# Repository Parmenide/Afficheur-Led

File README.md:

# Élèvage - Afficheur Led.

Un afficheur à diodes électroluminescentes pour faciliter l'appel et la consultation de classes dans une cour d'établissement scolaire du premier cycle du secondaire.

- [Description](#description-)
- [Péripheriques](#périphériques-)
- [Caractéristiques techniques :](caractéristiques-techniques-)
- [Composition matérielle :](#composition-matérielle-)
- [Procédure d'utilisation](#procédure-dutilisation-)
- [Sécurité](#sécurité-)
- [Notes complémentaires](notes-complementaires-)
- [Versions et mises à jours](#versions-et-mises-à-jours)
- [Explications résumée du fonctionnement](#explication-résumée-du-fonctionnement)
- [Illustrations](#illustrations)

## Description :

Cet afficheur à diodes électroluminescentes a pour fonction de fournir au service de vie scolaire d'un collège un support de communication simplifié avec les élèves, en particulier pour l'appel des classes à la cantine ou au réfectoire. Celui-ci par ailleurs, offre aux élèves un moyens aisé de se rapporter aux informations communiquées.
L'appareil affiche alors les classes souhaitées (de la 6eme à la 3eme reparties en classes identifiées de A à E) relativement à un tableau de commande qui transmet par radio-fréquences l'appel effectué.
Les classes appelées sont affichées en rouge et clignotent pendant 5 minutes avant de se stabiliser. Cela afin de distinguer les classes les plus récemment appelées des plus anciennes.

## Périphériques :

* Afficheur à diodes électroluminescentes
* Tableau de commande
* Relais

## Caractéristiques techniques :

 • | Afficheur | Tableau de commande | Relais
------------ | ------------ | ------------- | -------------
Tension de fonctionnement | 220v             | 220v            | 220v
Dimensions (≈)            | 1265mm/260mm/60mm | 225mm/160mm/50mm | ?mm/?mm/?mm
Emission/réception min.   | 100m             | 100m             | 100m
Emission/réception max    | 100m             | 100m             | 100m

## Composition matérielle :

* Afficheur
    * Cable étamé 26 AWG ≈20m
    * 777x leds 620\~625nm, 150\~200mcd, 1.8\~2.2v, 20mA.
    * 5x Panneaux MDF, A3, épaisseur : 3mm.
    * 3x SN74HC595
    * 20x P2N2222A
    * 20x Resistances 1KΩ
    * 4x Connecteur mâle (KF2510)
    * 4x Connecteur femelle (KF2510)
    * 20x Broches à sertirs (KF2510)
    * 1x PCB prototype 120mm/80mm
    * 1x Arduino-pro-mini 5V (ATMEGA 328)
    * 1x Récepteur RF 440mhz (HCN67)
    * 1x Antenne (170mm)
    * 200x Resistances 220Ω
    * 1x Transformateur AC/DC, 5V, 8A

* Tableau de commandes
    * 1x Cable étamé 26 AWG ≈1m
    * 20x led 620\~625nm, 150\~ 200mcd, 1.8\~ 2.2v, 20mA.
    * 1x Arduino-pro-mini 5V (ATMEGA 328)
    * 2x Panneaux MDF, A3, épaisseur : 3mm
    * Cable étamé 26 AWG ≈1m
    * Cable étamé 30 AWG ≈1m
    * 1x L7805
    * 2x CD4051
    * 20x Interupteur (MTS 101)
    * 2x Embases (DC3-10)
    * 2x Connecteurs (FC-10)
    * 1x PCB prototype 90mm/70mm
    * 1x Emeteur RF 440mhz (HC34C)
    * 1x Antenne (170mm)
    * 1x Transformateur AC/DC, 12V, 1A
    
* Relais
    * 2x led 620\~625nm, 150\~ 200mcd, 1.8\~ 2.2v, 20mA.
    * 1x Arduino-pro-mini 5V (ATMEGA 328)
    * 1x L7805
    * 1x PCB prototype 90mm/70mm
    * 1x Récepteur RF 440mhz (HCN67)
    * 1x Emeteur RF 440mhz (HC34C)
    * 2x Antenne (170mm)
    * 1x Transformateur AC/DC, 12V, 500mA

## Procédure d'utilisation :
L'utilisation demeure des plus simples : lorsque les deux appareils sont sous tensions, l'activation d'une classe sur le tableau de commandes allume la classe correspondante sur le panneau d'affichage. Les classes appelées clignotes pendant cinq minutes avant de rester allumées, cela afin de distinguer les classes récemment appelées des plus anciennes.

## Sécurité :
Si l'appareil est conçu pour résister aux projections d'eau et à l'humidité, il n'est pas conçu pour être immergé dans un liquide.

## Notes complémentaires :
Cet afficheur fut conçu avec les moyens techniques à disposition, à savoir une découpeuse laser pour le recouvrement qui contraint à une surface de découpe de la taille d'un A3 maximum.
Du côté électronique, là aussi le manque de moyens ont conduit à des choix spécifiques. Ainsi, à defaut de pouvoir graver un circuit sur une plaque de cuivre, il fut choisi d'utiliser des cartes de prototypage ainsi que des modules plutôt que des composants (AT-MEGA et radios-transmeteurs notamment).
L'afficheur serait alors sûrement d'autant mieux conçu s'il pouvait ne pas être soumis aux contraintes précédemment évoquées et donc permettre la découpe en une seule pièce des faces de l'afficheur, ainsi que de proposer un circuit plus abouti pour l'électronique.

Pour plusieurs autres raisons diverses, il fut choisi de composer des lettres et chiffres par plusieurs leds juxtaposés. Ce choix conduit à de lourdes opérations de fabrication. De plus, il n'est pas sans augmenter le risque de défaillance du système complet puisque, chaque led (777 au total) est potentiellement sujet à un risque de disfonctionnement. Réfléchir à un système moins complexe, mais tout aussi efficace serait alors sûrement souhaitable dans l'amélioration de cet objet.

Du coté logiciel, des améliorations sont sûrement aussi à envisager :
- Inverser les valeurs envoyé et reçu par le récepteur qui sont contraire à l'usage habituel, rendant le code parfois contre-intuitif (en effet, les 0 signifient ouverts et les 1 fermés dans la programmation actuelle)
- Ajouter un système de gestion par le biais du moniteur permettant de modifier le temps de clignotement ou la puissance des leds.
- Synchroniser le clignotement des leds pour l'afficheur

Afin de permettre d'éventuelles améliorations, les fichiers originaux de découpe ainsi que les fichiers correspondant aux circuits imprimé sont disponibles dans ce Git.

## Versions et mises à jours
L'ensemble est diffusé initialement dans sa version 1.0. C'est cette version qui accompagne l'appareil initialement fabriqué.
Dans le souci de proposer des améliorations sans contraindre l'utilisation et l'entretient de l'appareil initialement conçu, la version 1.0 restera acessible en plus des versions mises à jours.
Pour d'éventuelles mises à jour de la programmation des différents ATMEGA, il faudra se munir d'un programmateur UART (sur la base d'un microcontrôleur cp2101 par exemple).

## Explication résumée du fonctionnement.
### Tableau de bord
#### Menuiserie
- Conçu à partir de plans de découpe réalisés par ordinateur, c'est à partir d'une surface limitée à un A3 que fut découpé au laser les éléments du tableau de bord.
- Les interrupteurs, circuits de fils ainsi que les leds incrustés, furent montés sur le panneau avant son assemblage. Cela fait, les autres parties du tableau de bord furent assemblés par collage puis peints avant d'ajouter la face avant et les interrupteurs montés sur celui-ci.
#### Électronique
- 20 circuits sous tensions comprenant une led et un interrupteur constitue chaque boutons correspondant à chaque classe du tableau de bord.
- Sur chacun de ces circuits, un raccord à une broche du microcontrôleur (ATMEGA325) est effectué.
- Le microcontrôleur ne comprenant pas assez d'entrés/sorties, il fut choisi d'utiliser un multiplexeur/demultiplexeur (CD4051 ou SN74HC595) permettant par quelques broches de commander ou recevoir plusieurs signaux.
- Chaque signaux reçu par le microcontrôleur est rapporté à un bit nul ou positif (ouvert ou fermé) identifiant chaque classe à allumer ou éteindre.
- Ces signaux mémorisés dans un tableau, sont envoyés par le module de radio-frequence (À l'aide de la bibliotheque [VirtualWire](http://www.airspayce.com/mikem/arduino/VirtualWire.pdf))
### Afficheur
#### Menuiserie
- Conçu à partir de plans de découpe réalisés par ordinateur, c'est à partir d'une surface limitée à un A3 que fut découpé au laser les éléments de l'afficheur.
- Dans un premier temps, les éléments structurels de l'afficheur furent peints, puis les leds ajoutés sur les éléments de la façade de l'afficheur avant d'êtres englués pour les maintenir en place.
- Des fils dénudés furent ensuite glissés entre les différentes anodes puis cathode des leds avant de souder ces fils pour raccorder les leds entres elles (par groupe de 4 leds monté en série). Est ensuite soudé des fils aux différents groupes de leds pour permettre leurs raccordements au microcontrôleur.
- À l'aide de tasseau de 10x10mm placés aux arêtes de l'afficheur, les différents éléments de la façade sont rassemblés et collés.
- L'ensemble est vernis et raccordé à l'électronique.
#### Électronique
- 20 circuits sous tensions correspondant à chaque classe et comprenant en moyenne 30 leds répartie en séries de 4 leds rassemblés en parallèles. Chacun de ces circuits est ouvert et comporte un fil qui une fois raccordé à l'anode du générateur permet fermer le circuit et donc d'afficher la classe correspondante.
- Chacun de ces fils est raccordé au collecteur d'un transistor (P2N2222A) qui a son émetteur raccordé à l'anode du générateur. En alimentant ou non la base du transistor, on peut alors utiliser celui-ci comme interrupteur électronique.
- Chaque base de chaque transistor (20 en tout) est raccordée à une borne du microcontrôleur par le biais d'un multiplexeur/demultiplexeur.
- De ce, à la réception du signal, chaque transistor est alimenté ou non à sa base selon l'information recu (0 ou 1).

## Illustrations
### Panneau d'affichage V 1.0
     
### Tableau de commandes V 1.0
 
### Mise en situation dans un collège de région tourangelle

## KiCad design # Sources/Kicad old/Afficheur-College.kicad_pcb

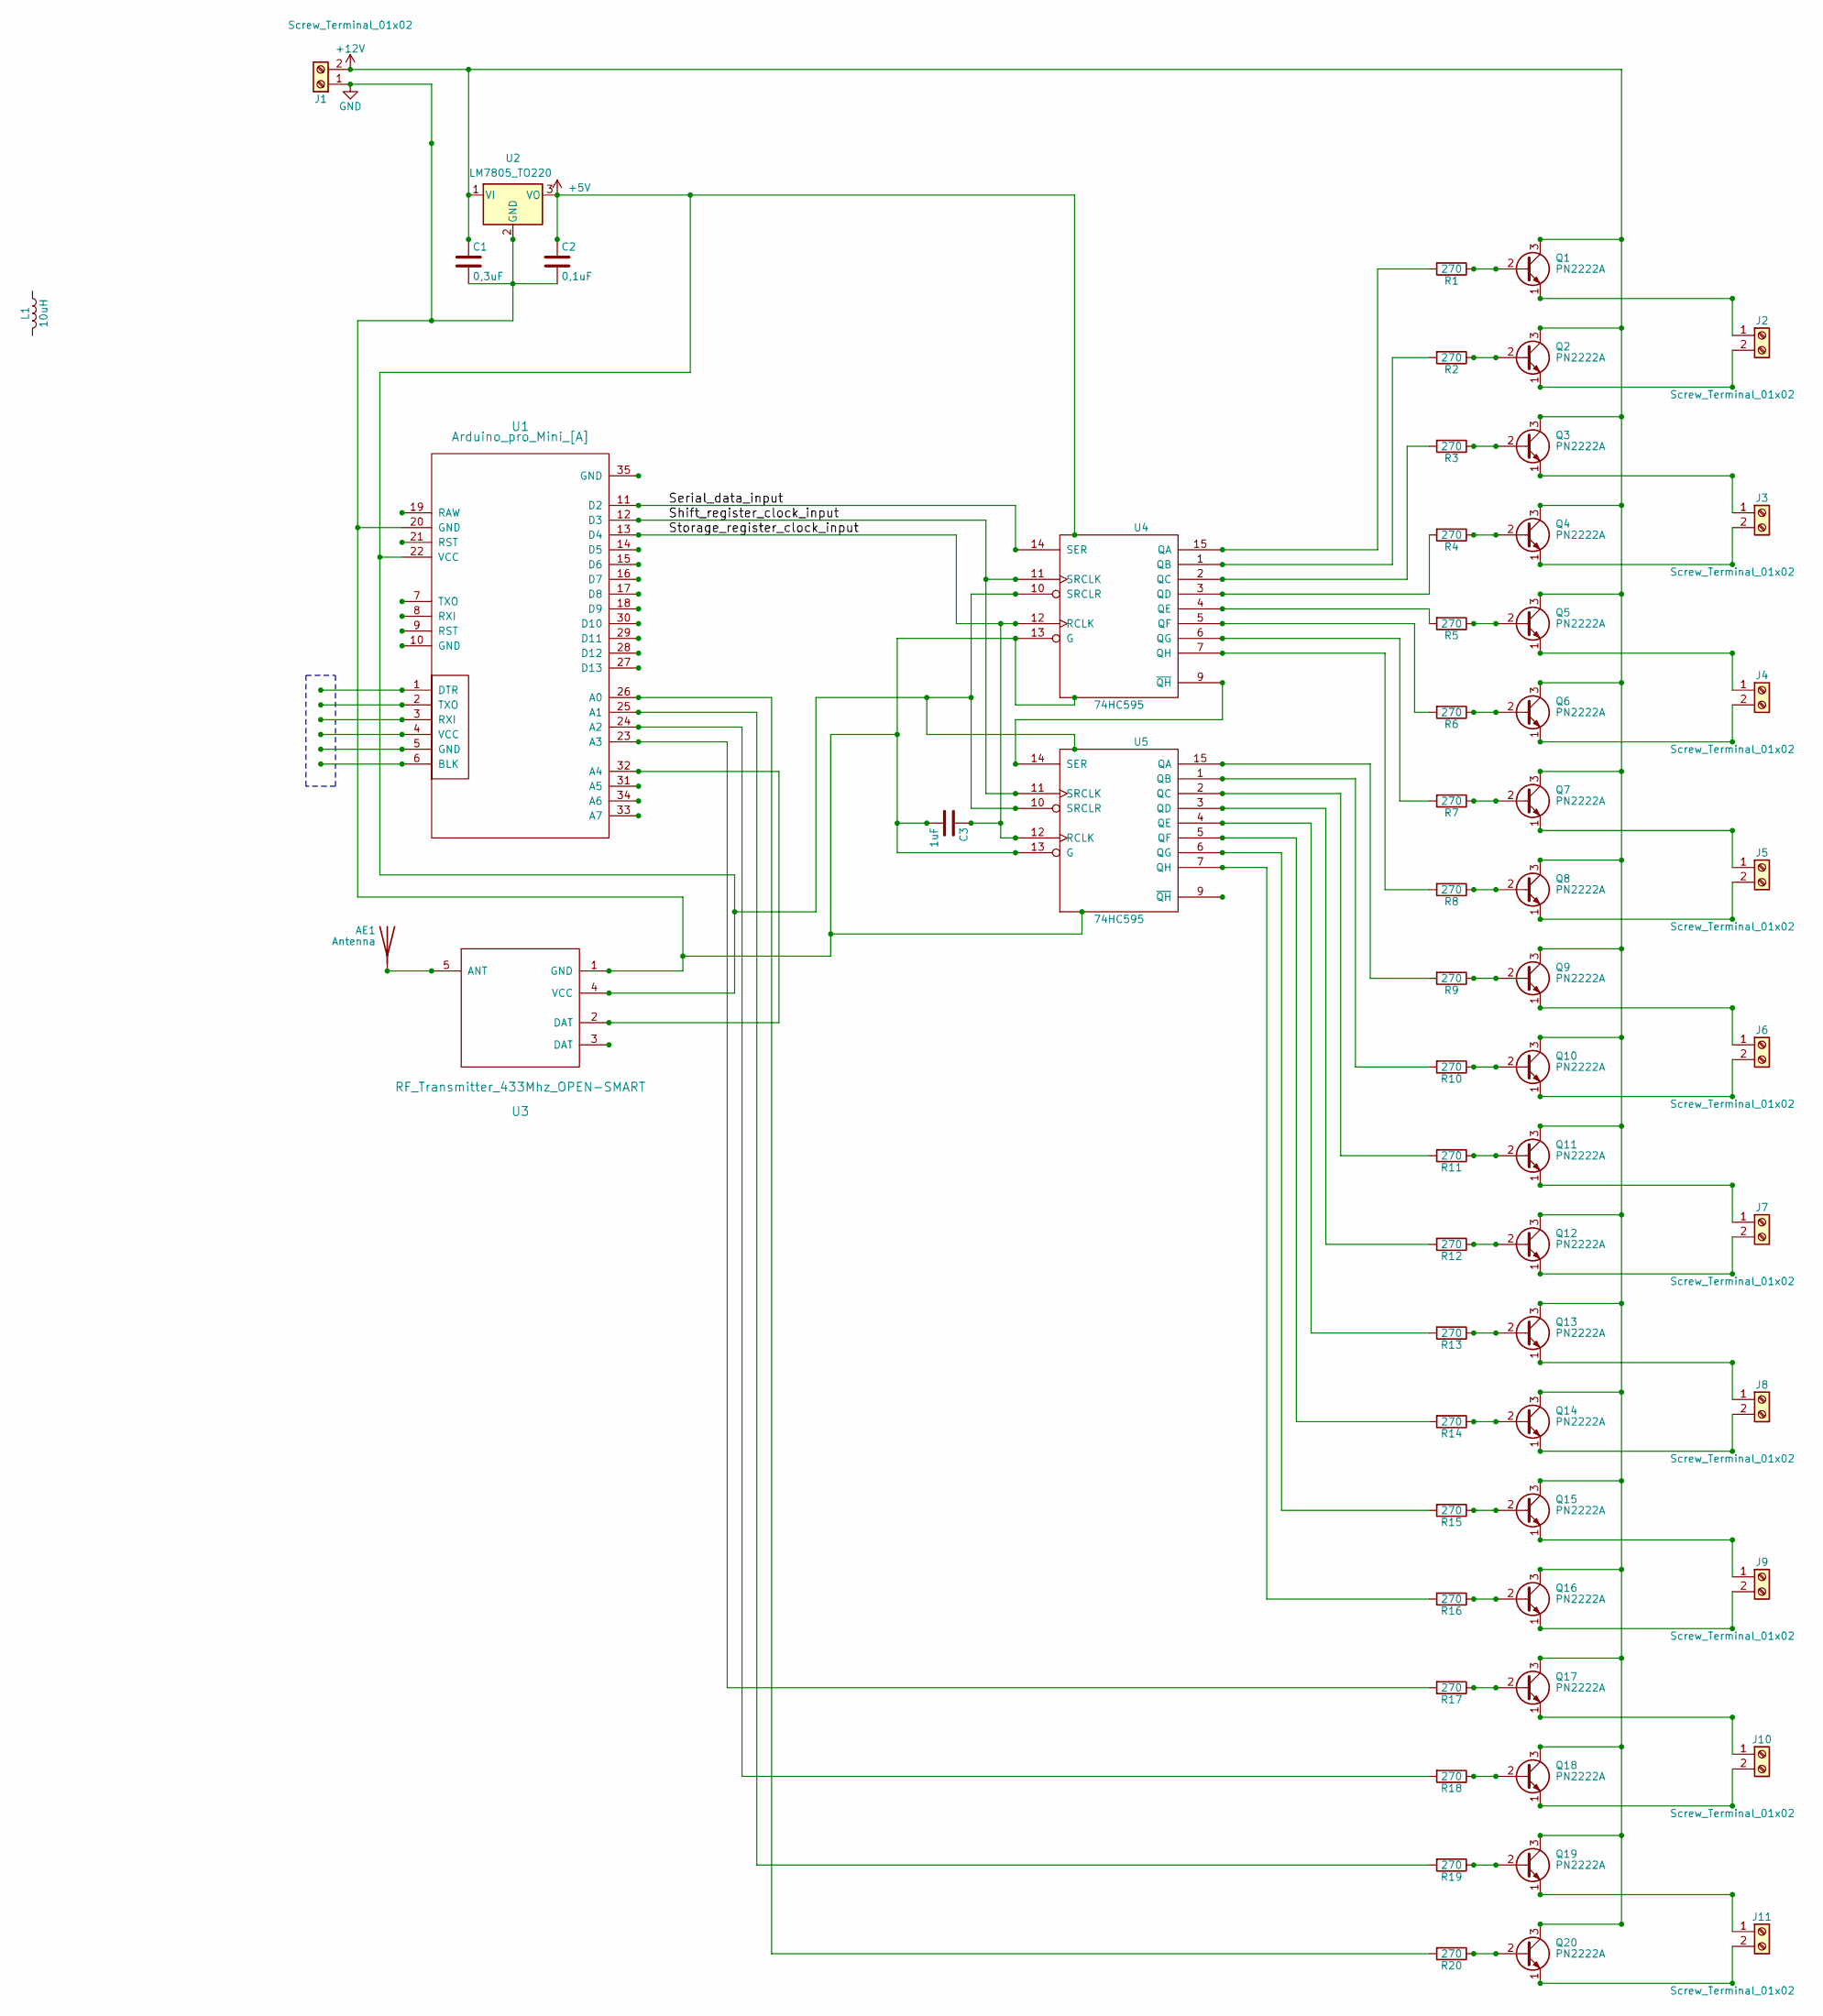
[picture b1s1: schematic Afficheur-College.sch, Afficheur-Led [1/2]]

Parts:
AE1: Antenna; 1pin
C1: 0,3uF; C_Disc_D5.0mm_W2.5mm_P5.00mm
C2: 0,1uF; C_Disc_D5.0mm_W2.5mm_P5.00mm
C3: 1uF; C_Disc_D5.0mm_W2.5mm_P5.00mm
J1, J2, J3, J4, J5, J6, J7, J8, J9, J10, J11: Screw_Terminal_01x02; TerminalBlock_Pheonix_MPT-2.54mm_2pol
L1: 10uH
Q1, Q2, Q3, Q4, Q5, Q6, Q7, Q8, Q9, Q10, Q11, Q12, Q13, Q14, Q15, Q16, Q17, Q18, Q19, Q20: PN2222A; TO-92_Inline_Wide
R1, R2, R3, R4, R5, R6, R7, R8, R9, R10, R11, R12, R13, R14, R15, R16, R17, R18, R19, R20: 270; R_Axial_DIN0207_L6.3mm_D2.5mm_P10.16mm_Horizontal
U1: Arduino_pro_Mini_[A]; Arduino-Pro-Mini
U2: LM7805_TO220; TO-220-3_Vertical
U3: RF_Transmitter_433Mhz_OPEN-SMART; RF-R
U4, U5: 74HC595; DIP-16_W7.62mm

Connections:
+5V: C2.1, U1.22 (VCC), U2.3 (VO), U3.4 (VCC), U4.10 (SRCLR), U4.16 (VCC), U5.10 (SRCLR), U5.16 (VCC)
/Serial_data_input: U1.11 (D2), U4.14 (SER)
/Shift_register_clock_input: U1.12 (D3), U4.11 (SRCLK), U5.11 (SRCLK)
/Storage_register_clock_input: C3.1, U1.13 (D4), U4.12 (RCLK), U5.12 (RCLK)
GND: C1.2, C2.2, C3.2, J1.1, U1.20 (GND), U2.2 (GND), U3.1 (GND), U4.8 (GND), U4.13 (G), U5.8 (GND), U5.13 (G)
unnamed: AE1.1, U3.5 (ANT)
unnamed: J2.1, Q1.1 (E)
unnamed: J2.2, Q2.1 (E)
unnamed: J3.1, Q3.1 (E)
unnamed: J3.2, Q4.1 (E)
unnamed: J4.1, Q5.1 (E)
unnamed: J4.2, Q6.1 (E)
unnamed: J5.1, Q7.1 (E)
unnamed: J5.2, Q8.1 (E)
unnamed: J6.1, Q9.1 (E)
unnamed: J6.2, Q10.1 (E)
unnamed: J7.1, Q11.1 (E)
unnamed: J7.2, Q12.1 (E)
unnamed: J8.1, Q13.1 (E)
unnamed: J8.2, Q14.1 (E)
unnamed: J9.1, Q15.1 (E)
unnamed: J9.2, Q16.1 (E)
unnamed: J10.1, Q17.1 (E)
unnamed: J10.2, Q18.1 (E)
unnamed: J11.1, Q19.1 (E)
unnamed: J11.2, Q20.1 (E)
unnamed: Q1.2 (B), R1.1
unnamed: Q2.2 (B), R2.1
unnamed: Q3.2 (B), R3.1
unnamed: Q4.2 (B), R4.1
unnamed: Q5.2 (B), R5.1
unnamed: Q6.2 (B), R6.1
unnamed: Q7.2 (B), R7.1
unnamed: Q8.2 (B), R8.1
unnamed: Q9.2 (B), R9.1
unnamed: Q10.2 (B), R10.1
unnamed: Q11.2 (B), R11.1
unnamed: Q12.2 (B), R12.1
unnamed: Q13.2 (B), R13.1
unnamed: Q14.2 (B), R14.1
unnamed: Q15.2 (B), R15.1
unnamed: Q16.2 (B), R16.1
unnamed: Q17.2 (B), R17.1
unnamed: Q18.2 (B), R18.1
unnamed: Q19.2 (B), R19.1
unnamed: Q20.2 (B), R20.1
unnamed: R1.2, U4.15 (QA)
unnamed: R2.2, U4.1 (QB)
unnamed: R3.2, U4.2 (QC)
unnamed: R4.2, U4.3 (QD)
unnamed: R5.2, U4.4 (QE)
unnamed: R6.2, U4.5 (QF)
unnamed: R7.2, U4.6 (QG)
unnamed: R8.2, U4.7 (QH)
unnamed: R9.2, U5.15 (QA)
unnamed: R10.2, U5.1 (QB)
unnamed: R11.2, U5.2 (QC)
unnamed: R12.2, U5.3 (QD)
unnamed: R13.2, U5.4 (QE)
unnamed: R14.2, U5.5 (QF)
unnamed: R15.2, U5.6 (QG)
unnamed: R16.2, U5.7 (QH)
unnamed: R17.2, U1.23 (A3)
unnamed: R18.2, U1.24 (A2)
unnamed: R19.2, U1.25 (A1)
unnamed: R20.2, U1.26 (A0)
unnamed: U1.32 (A4), U3.2 (DAT)
unnamed: U4.9 (~QH), U5.14 (SER)

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
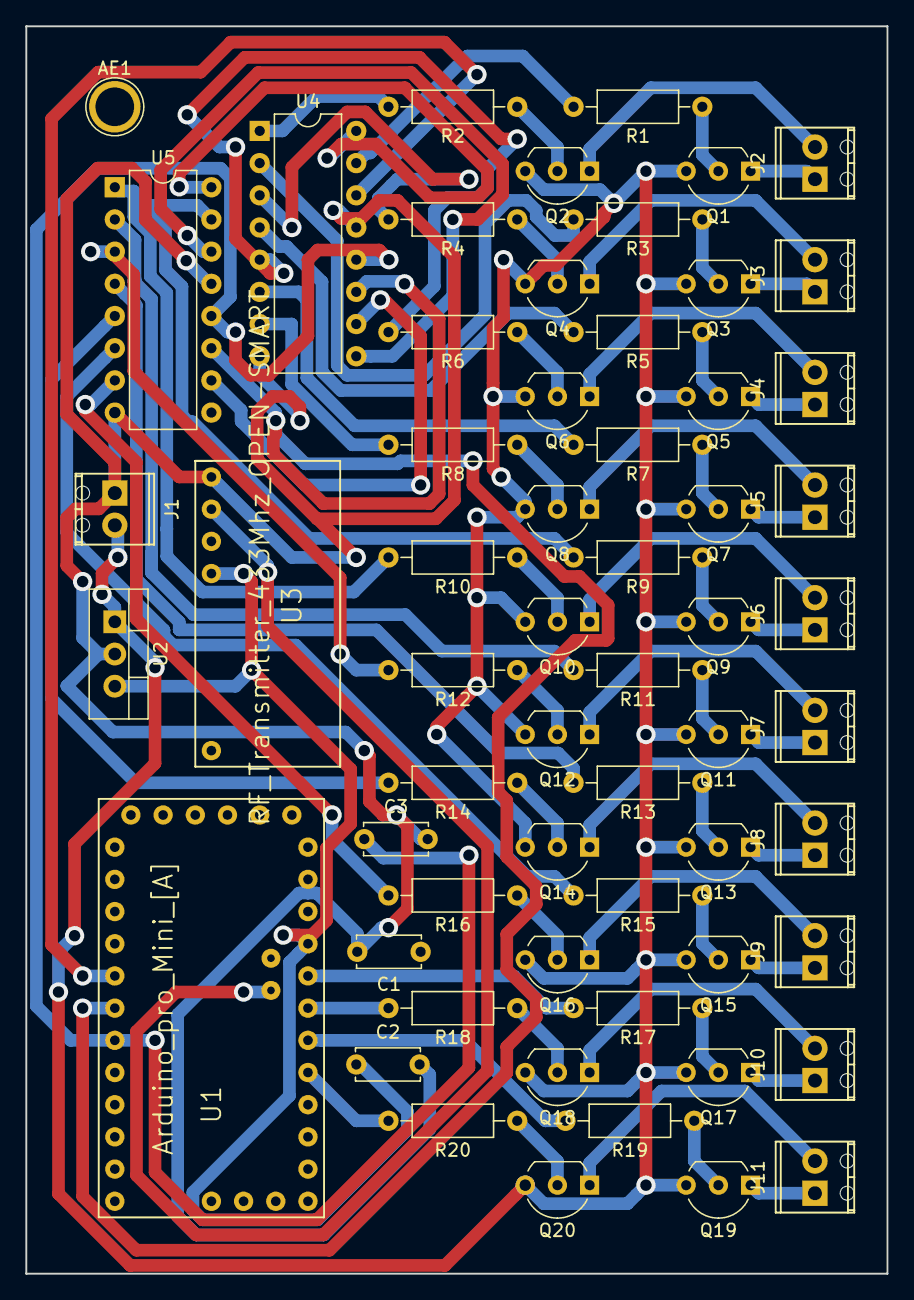
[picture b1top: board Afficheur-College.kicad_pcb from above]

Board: 2 copper layers, 67.9 x 98.4 mm, 60 parts (0 on the bottom side), 69 nets.

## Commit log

2017-11-17 Init Readme
2017-11-17 Update Readme (Init2)
2017-11-19 Datasshets, SVG & OBJ
2017-11-20 Circuits electroniques (kicad)
2017-11-20 readme
2017-12-30 Update 30/12/17
2018-02-03 new commit
2018-04-18 Clean up #01
2018-04-18 Update
    Ajout de quelques images
